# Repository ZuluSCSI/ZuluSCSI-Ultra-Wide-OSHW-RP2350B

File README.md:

ZuluSCSI™ Ultra Wide OSHW - Community Edition - Open Source Hardware
========================
ZuluSCSI Ultra Wide is the worlds first* OSHW _ultra wide_ SCSI emulator. It's an open-source alternative to our commercially-available [ZuluSCSI Wide](https://shop.rabbitholecomputing.com/blogs/news/zuluscsi-wide-33mb-sec-wide-scsi-emulator), which uses much higher-quality printed circuit boards and largely higher-quality components. 

ZuluSCSI Ultra Wide runs unmodified [ZuluSCSI Wide firmware](https://github.com/ZuluSCSI/ZuluSCSI-firmware/releases).

This repository contains the KiCAD 9 schematic and PCB design files for an Open Source Hardware variant of the RP2350B-based ZuluSCSI™ SCSI to SD storage emulator, derived from George Mezzomo's incomplete-at-time-of-forking [RP2350B-based GBSCSI2 wide board](https://github.com/GeorgeRudolf/GBSCSI2/tree/main/rp2350_HD68_3.5). 

Numerous small improvements to routing, pinouts, expansion headers, and power circuitry have been made. As always, firmware for ZuluSCSI is available at http://github.com/ZuluSCSI/ZuluSCSI-firmware

This hardware design is licensed under the terms of the strongly reciprocal CERN OHL-S V2 license, which can be viewed in full at https://ohwr.org/cern_ohl_s_v2.txt and https://ohwr.org/cern_ohl_s_v2.pdf. 

The Rev 2026b ZuluSCSI Ultra Wide OSHW design is [OSHWA-certified](https://certification.oshwa.org/us002798.html)

ZuluSCSI™ is a registered trademark of Rabbit Hole Computing, and may not be used commercially without the express written consent of Rabbit Hole Computing. Individuals producing ZuluSCSI boards for personal use are hereby granted permission to use the ZuluSCSI trademark in a noncommercial capacity.

_Any_ use of the ZuluSCSI trademark in a **commercial** context requires prior written consent from Rabbit Hole Computing.

* that we know of :)

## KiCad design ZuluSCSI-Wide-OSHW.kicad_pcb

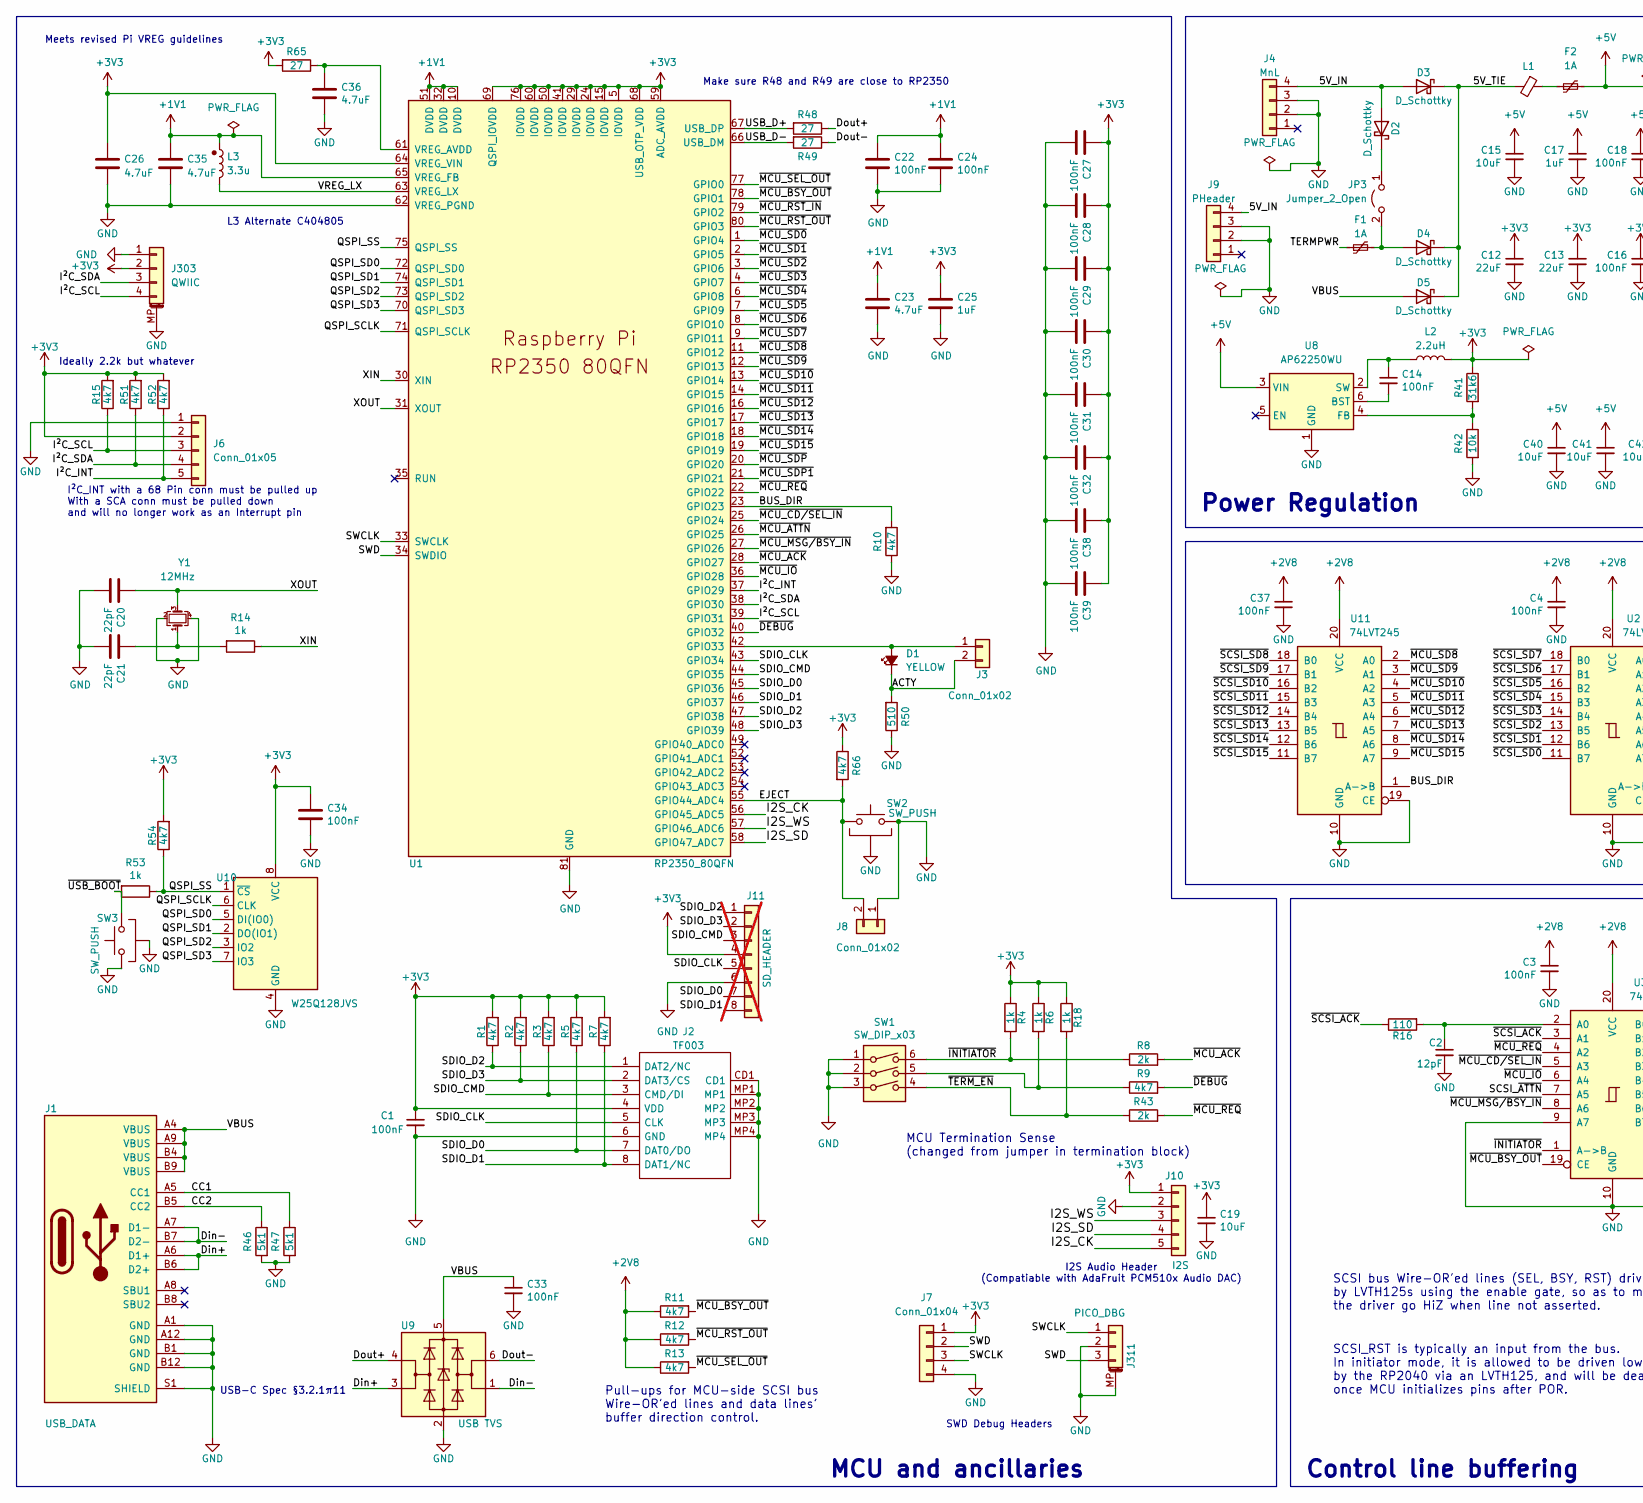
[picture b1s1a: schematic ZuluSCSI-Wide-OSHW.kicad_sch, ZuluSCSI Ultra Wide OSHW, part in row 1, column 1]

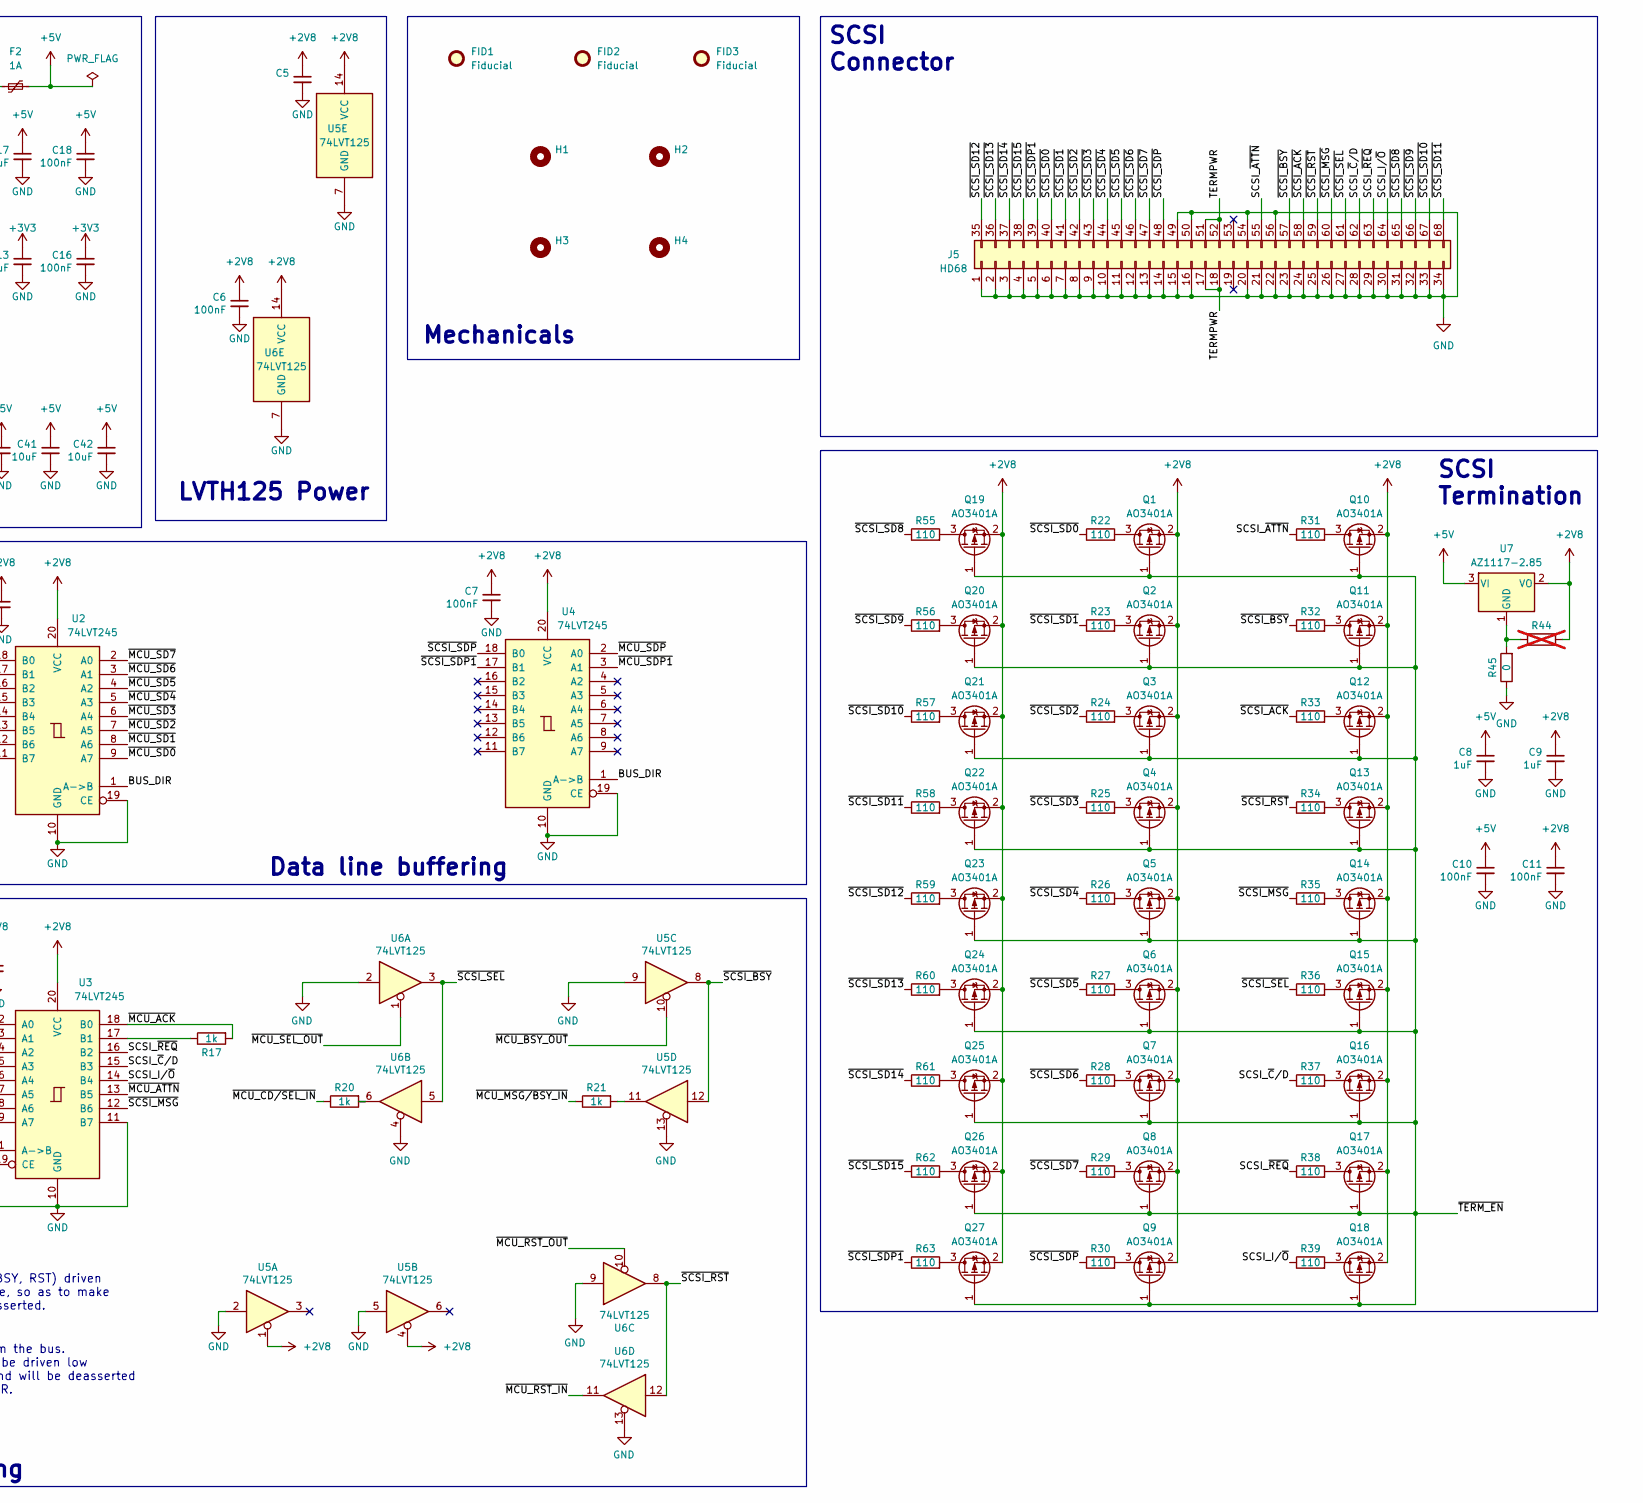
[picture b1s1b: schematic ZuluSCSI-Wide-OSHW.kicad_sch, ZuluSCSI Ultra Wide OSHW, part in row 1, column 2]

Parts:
C1, C3, C4, C5, C6, C7, C10, C11, C14, C16, C18, C37: 100nF; C_0603_1608Metric; LCSC C14663
C2: 12pF; C_0603_1608Metric; LCSC C38523
C8, C9, C17: 1uF; C_0603_1608Metric; LCSC C15849
C12, C13: 22uF; C_0603_1608Metric; LCSC C59461
C15, C19, C40, C41, C42: 10uF; C_0603_1608Metric; LCSC C96446
C20, C21: 22pF; C_0402_1005Metric; LCSC C1555
C22, C24, C27, C28, C29, C30, C31, C32, C33, C34, C38, C39: 100nF; C_0402_1005Metric; LCSC C307331
C23: 4.7uF; C_0402_1005Metric; LCSC C23733
C25: 1uF; C_0402_1005Metric; LCSC C52923
C26, C35: 4.7uF; C_0603_1608Metric; LCSC Part # C19666
C36: 4.7uF; C_0402_1005Metric; LCSC Part # C23733
D1: YELLOW; LED_0603_1608Metric; LCSC C72038
D2, D3, D4, D5: D_Schottky; D_SOD-123; LCSC C82544
F1, F2: 1A; Fuse_0805_2012Metric; LCSC C70061
FID1, FID2, FID3: Fiducial; Fiducial_0.5mm_Mask1mm; LCSC N/A
H1, H2, H3, H4: MH2.5_NPTH; LCSC N/A
J1: USB_DATA; USB_C_Receptacle_HRO_TYPE-C-31-M-12; LCSC C165948
J2: TF003; TF01A; LCSC C5155563
J3, J8: Conn_01x02; PinHeader_1x02_P2.54mm_Vertical; LCSC N/A
J4: MnL; DRVPWR; LCSC N/A
J5: HD68; 5787169-7; LCSC N/A
J6: Conn_01x05; PinHeader_1x05_P2.54mm_Vertical; LCSC N/A
J7: Conn_01x04; PinHeader_1x04_P2.54mm_Vertical; LCSC N/A
J9: PHeader; PinHeader_1x04_P2.54mm_Vertical; LCSC N/A
J10: I2S; PCM510x_1x05_P2.54mm_Vertical
J11: SD_HEADER; PinHeader_1x08_P2.54mm_Vertical; not fitted
J303: QWIIC; JST_SH_BM04B-SRSS-TB_1x04-1MP_P1.00mm_Vertical; LCSC C160390
J311: PICO_DBG; JST_SH_BM03B-SRSS-TB_1x03-1MP_P1.00mm_Vertical; LCSC C160389
JP3: Jumper_2_Open; PinHeader_2x01_P2.54mm_Vertical; LCSC N/A
L1: Ferrite_Bead_Small; L_0603_1608Metric; LCSC C1002
L2: 2.2uH; L_1008_2520Metric_Pad1.43x2.20mm_HandSolder; PartNumber DFE252012P-2R2M=P2; LCSC C86092
L3: 3.3u; L_pol_2016; PartNumber AOTA-B201610S3R3-101-T; digikey 535-AOTA-B201610S3R3-101-TTR-ND
Q1, Q2, Q3, Q4, Q5, Q6, Q7, Q8, Q9, Q10, Q11, Q12, Q13, Q14, Q15, Q16, Q17, Q18, Q19, Q20, Q21, Q22, Q23, Q24, Q25, Q26, Q27: AO3401A; SOT-23; LCSC C15127
R1, R2, R3, R5, R7, R9, R10, R11, R12, R13, R15, R51, R52, R54, R66: 4k7; R_0603_1608Metric; LCSC C23162
R4, R6, R17, R18, R20, R21: 1k; R_0603_1608Metric; LCSC C21190
R8, R43: 2k; R_0603_1608Metric; LCSC C22975
R14, R53: 1k; R_0402_1005Metric; LCSC C11702
R16, R22, R23, R24, R25, R26, R27, R28, R29, R30, R31, R32, R33, R34, R35, R36, R37, R38, R39, R55, R56, R57, R58, R59, R60, R61, R62, R63: 110; R_0603_1608Metric; LCSC C22781
R41: 31k6; R_0603_1608Metric; LCSC C25967
R42: 10k; R_0603_1608Metric; LCSC C25804
R44: R_0603_1608Metric; LCSC N/A; not fitted
R45: 0; R_0603_1608Metric; LCSC C21189
R46, R47: 5k1; R_0402_1005Metric; LCSC C25905
R48, R49, R65: 27; R_0402_1005Metric; LCSC C25092
R50: 510; R_0603_1608Metric; LCSC C23193
SW1: SW_DIP_x03; SW_DIP_SPSTx03_Slide_6.7x9.18mm_W8.61mm_P2.54mm_LowProfile; PartNumber 219-3MSTR; LCSC C319040
SW2, SW3: SW_PUSH; SW-SMD_GT-TC108A-H034-L1S; LCSC C22396279
U1: RP2350_80QFN; RP2350-QFN-80-1EP_10x10_P0.4mm_EP3.4x3.4mm_ThermalVias; LCSC Part # C42415655
U2, U3, U4, U11: 74LVT245; SSOP-20_5.3x7.2mm_P0.65mm; LCSC C74214
U5, U6: 74LVT125; TSSOP-14_4.4x5mm_P0.65mm; LCSC C7042
U7: AZ1117-2.85; SOT-223-3_TabPin2; LCSC C14791
U8: AP62250WU; TSOT-23-6; LCSC C5184228
U9: USB TVS; SOT-23-6; LCSC C2827654
U10: W25Q128JVS; SOIC-8_5.23x5.23mm_P1.27mm; LCSC C97521
Y1: 12MHz; Crystal_SMD_3225-4Pin_3.2x2.5mm; PartNumber ABM8-272-T3; LCSC C20625731

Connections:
+1V1: C22.1, C23.1, C24.1, C35.1, L3.1, U1.10 (DVDD), U1.32 (DVDD), U1.51 (DVDD), U1.65 (VREG_FB)
+2V8: C3.1, C4.1, C5.1, C6.1, C7.1, C9.1, C11.1, C37.1, Q1.2 (S), Q2.2 (S), Q3.2 (S), Q4.2 (S), Q5.2 (S), Q6.2 (S), Q7.2 (S), Q8.2 (S), Q9.2 (S), Q10.2 (S), Q11.2 (S), Q12.2 (S), Q13.2 (S), Q14.2 (S), Q15.2 (S), Q16.2 (S), Q17.2 (S), Q18.2 (S), Q19.2 (S), Q20.2 (S), Q21.2 (S), Q22.2 (S), Q23.2 (S), Q24.2 (S), Q25.2 (S), Q26.2 (S), Q27.2 (S), R11.1, R12.1, R13.1, R44.2, U2.20 (VCC), U3.20 (VCC), U4.20 (VCC), U5.1, U5.4, U5.14 (VCC), U6.14 (VCC), U7.2 (VO), U11.20 (VCC)
+3V3: C1.1, C12.1, C13.1, C16.1, C19.1, C25.1, C26.1, C27.1, C28.1, C29.1, C30.1, C31.1, C32.1, C34.1, C38.1, C39.1, J2.4 (VDD), J6.2, J7.1, J10.1, J11.4, J303.2, L2.2, R1.2, R2.2, R3.2, R4.1, R5.2, R6.1, R7.2, R15.2, R18.1, R41.1, R51.2, R52.2, R54.2, R65.2, R66.1, U1.5 (IOVDD), U1.15 (IOVDD), U1.24 (IOVDD), U1.29 (IOVDD), U1.41 (IOVDD), U1.50 (IOVDD), U1.59 (ADC_AVDD), U1.60 (IOVDD), U1.64 (VREG_VIN), U1.68 (USB_OTP_VDD), U1.69 (QSPI_IOVDD), U1.76 (IOVDD), U10.8 (VCC)
+5V: C8.1, C10.1, C15.1, C17.1, C18.1, C40.1, C41.1, C42.1, F2.2, U7.3 (VI), U8.3 (VIN)
/5V_IN: D2.2 (A), D3.2 (A), J4.4, J9.4
/5V_TIE: D3.1 (K), D4.1 (K), D5.1 (K), L1.2
/ACTY: D1.1 (K), J3.2, R50.2
/BUS_DIR: R10.2, U1.23 (GPIO23), U2.1 (A->B), U4.1 (A->B), U11.1 (A->B)
/CC1: J1.A5 (CC1), R47.1
/CC2: J1.B5 (CC2), R46.1
/Din+: J1.A6 (D1+), J1.B6 (D2+), U9.3 (I/O2)
/Din-: J1.A7 (D1-), J1.B7 (D2-), U9.1 (I/O1)
/Dout+: R48.1, U9.4 (I/O2)
/Dout-: R49.1, U9.6 (I/O1)
/EJECT: J8.2, R66.2, SW2.2, U1.55 (GPIO44_ADC4)
/I2S_CK: J10.5, U1.56 (GPIO45_ADC5)
/I2S_SD: J10.4, U1.58 (GPIO47_ADC7)
/I2S_WS: J10.3, U1.57 (GPIO46_ADC6)
/I²C_INT: J6.5, R52.1, U1.37 (GPIO29)
/I²C_SCL: J6.3, J303.4, R15.1, U1.39 (GPIO31)
/I²C_SDA: J6.4, J303.3, R51.1, U1.38 (GPIO30)
/QSPI_SCLK: U1.71 (QSPI_SCLK), U10.6 (CLK)
/QSPI_SD0: U1.72 (QSPI_SD0), U10.5 (DI(IO0))
/QSPI_SD1: U1.74 (QSPI_SD1), U10.2 (DO(IO1))
/QSPI_SD2: U1.73 (QSPI_SD2), U10.3 (IO2)
/QSPI_SD3: U1.70 (QSPI_SD3), U10.7 (IO3)
/QSPI_SS: R53.1, R54.1, U1.75 (QSPI_SS), U10.1 (~CS)
/SCSI_I/~O: J5.64, R39.1, U3.14 (B4)
/SCSI_~ATTN: J5.55, R31.1, U3.7 (A5)
/SCSI_~C/D: J5.62, R37.1, U3.15 (B3)
/SCSI_~REQ: J5.63, R38.1, U3.16 (B2)
/SDIO_CLK: J2.5 (CLK), J11.5, U1.43 (GPIO34)
/SDIO_CMD: J2.3 (CMD/DI), J11.3, R3.1, U1.44 (GPIO35)
/SDIO_D0: J2.7 (DAT0/DO), J11.7, R5.1, U1.45 (GPIO36)
/SDIO_D1: J2.8 (DAT1/NC), J11.8, R7.1, U1.46 (GPIO37)
/SDIO_D2: J2.1 (DAT2/NC), J11.1, R1.1, U1.47 (GPIO38)
/SDIO_D3: J2.2 (DAT3/CS), J11.2, R2.1, U1.48 (GPIO39)
/SWCLK: J7.3, J311.1, U1.33 (SWCLK)
/SWD: J7.2, J311.3, U1.34 (SWDIO)
/TERMPWR: F1.1, J5.17, J5.18, J5.51, J5.52
/USB_D+: R48.2, U1.67 (USB_DP)
/USB_D-: R49.2, U1.66 (USB_DM)
/VBUS: C33.1, D5.2 (A), J1.A4 (VBUS), J1.A9 (VBUS), J1.B4 (VBUS), J1.B9 (VBUS), U9.5 (VBUS)
/VREG_LX: L3.2, U1.63 (VREG_LX)
/XIN: R14.1, U1.30 (XIN)
/XOUT: C20.1, U1.31 (XOUT), Y1.3
/~DEBUG: R9.2, U1.40 (GPIO32)
/~INITIATOR: R4.2, R8.1, SW1.6, U3.1 (A->B)
/~MCU_ACK: R8.2, R17.2, U1.28 (GPIO27), U3.18 (B0)
/~MCU_ATTN: U1.26 (GPIO25), U3.13 (B5)
/~MCU_BSY_OUT: R11.2, U1.78 (GPIO1), U3.19 (CE), U5.10
/~MCU_CD/SEL_IN: R20.1, U1.25 (GPIO24), U3.5 (A3)
/~MCU_IO: U1.36 (GPIO28), U3.6 (A4)
/~MCU_MSG/BSY_IN: R21.1, U1.27 (GPIO26), U3.8 (A6)
/~MCU_REQ: R43.2, U1.22 (GPIO22), U3.4 (A2)
/~MCU_RST_IN: U1.79 (GPIO2), U6.11
/~MCU_RST_OUT: R12.2, U1.80 (GPIO3), U6.10
/~MCU_SD0: U1.1 (GPIO4), U2.9 (A7)
/~MCU_SD1: U1.2 (GPIO5), U2.8 (A6)
/~MCU_SD2: U1.3 (GPIO6), U2.7 (A5)
/~MCU_SD3: U1.4 (GPIO7), U2.6 (A4)
/~MCU_SD4: U1.6 (GPIO8), U2.5 (A3)
/~MCU_SD5: U1.7 (GPIO9), U2.4 (A2)
/~MCU_SD6: U1.8 (GPIO10), U2.3 (A1)
/~MCU_SD7: U1.9 (GPIO11), U2.2 (A0)
/~MCU_SD8: U1.11 (GPIO12), U11.2 (A0)
/~MCU_SD9: U1.12 (GPIO13), U11.3 (A1)
/~MCU_SD10: U1.13 (GPIO14), U11.4 (A2)
/~MCU_SD11: U1.14 (GPIO15), U11.5 (A3)
/~MCU_SD12: U1.16 (GPIO16), U11.6 (A4)
/~MCU_SD13: U1.17 (GPIO17), U11.7 (A5)
/~MCU_SD14: U1.18 (GPIO18), U11.8 (A6)
/~MCU_SD15: U1.19 (GPIO19), U11.9 (A7)
/~MCU_SDP1: U1.21 (GPIO21), U4.3 (A1)
/~MCU_SDP: U1.20 (GPIO20), U4.2 (A0)
/~MCU_SEL_OUT: R13.2, U1.77 (GPIO0), U6.1
/~SCSI_ACK: J5.58, R16.1, R33.1, U3.3 (A1)
/~SCSI_BSY: J5.57, R32.1, U5.8, U5.12
/~SCSI_MSG: J5.60, R35.1, U3.12 (B6)
/~SCSI_RST: J5.59, R34.1, U6.8, U6.12
/~SCSI_SD0: J5.40, R22.1, U2.11 (B7)
/~SCSI_SD1: J5.41, R23.1, U2.12 (B6)
/~SCSI_SD2: J5.42, R24.1, U2.13 (B5)
/~SCSI_SD3: J5.43, R25.1, U2.14 (B4)
/~SCSI_SD4: J5.44, R26.1, U2.15 (B3)
/~SCSI_SD5: J5.45, R27.1, U2.16 (B2)
/~SCSI_SD6: J5.46, R28.1, U2.17 (B1)
/~SCSI_SD7: J5.47, R29.1, U2.18 (B0)
/~SCSI_SD8: J5.65, R55.1, U11.18 (B0)
/~SCSI_SD9: J5.66, R56.1, U11.17 (B1)
/~SCSI_SD10: J5.67, R57.1, U11.16 (B2)
/~SCSI_SD11: J5.68, R58.1, U11.15 (B3)
/~SCSI_SD12: J5.35, R59.1, U11.14 (B4)
/~SCSI_SD13: J5.36, R60.1, U11.13 (B5)
/~SCSI_SD14: J5.37, R61.1, U11.12 (B6)
/~SCSI_SD15: J5.38, R62.1, U11.11 (B7)
/~SCSI_SDP1: J5.39, R63.1, U4.17 (B1)
/~SCSI_SDP: J5.48, R30.1, U4.18 (B0)
/~SCSI_SEL: J5.61, R36.1, U6.3, U6.5
/~TERM_EN: Q1.1 (G), Q2.1 (G), Q3.1 (G), Q4.1 (G), Q5.1 (G), Q6.1 (G), Q7.1 (G), Q8.1 (G), Q9.1 (G), Q10.1 (G), Q11.1 (G), Q12.1 (G), Q13.1 (G), Q14.1 (G), Q15.1 (G), Q16.1 (G), Q17.1 (G), Q18.1 (G), Q19.1 (G), Q20.1 (G), Q21.1 (G), Q22.1 (G), Q23.1 (G), Q24.1 (G), Q25.1 (G), Q26.1 (G), Q27.1 (G), R18.2, R43.1, SW1.4
/~USB_BOOT: R53.2, SW3.2
GND: C1.2, C2.2, C3.2, C4.2, C5.2, C6.2, C7.2, C8.2, C9.2, C10.2, C11.2, C12.2, C13.2, C15.2, C16.2, C17.2, C18.2, C19.2, C20.2, C21.2, C22.2, C23.2, C24.2, C25.2, C26.2, C27.2, C28.2, C29.2, C30.2, C31.2, C32.2, C33.2, C34.2, C35.2, C36.2, C37.2, C38.2, C39.2, C40.2, C41.2, C42.2, J1.A1 (GND), J1.A12 (GND), J1.B1 (GND), J1.B12 (GND), J1.S1 (SHIELD), J2.6 (GND), J2.CD1, J2.MP1, J2.MP2, J2.MP3, J2.MP4, J4.2, J4.3, J5.1, J5.2, J5.3, J5.4, J5.5, J5.6, J5.7, J5.8, J5.9, J5.10, J5.11, J5.12, J5.13, J5.14, J5.15, J5.16, J5.20, J5.21, J5.22, J5.23, J5.24, J5.25, J5.26, J5.27, J5.28, J5.29, J5.30, J5.31, J5.32, J5.33, J5.34, J5.49, J5.50, J5.54, J5.56, J6.1, J7.4, J8.1, J9.2, J9.3, J10.2, J11.6, J303.1, J303.MP (MountPin), J311.2, J311.MP (MountPin), R10.1, R42.2, R45.1, R46.2, R47.2, R50.1, SW1.1, SW1.2, SW1.3, SW2.1, SW2.3 (MNT), SW3.1, SW3.3 (MNT), U1.62 (VREG_PGND), U1.81 (GND), U2.10 (GND), U2.19 (CE), U3.9 (A7), U3.10 (GND), U3.11 (B7), U4.10 (GND), U4.19 (CE), U5.2, U5.5, U5.7 (GND), U5.9, U5.13, U6.2, U6.4, U6.7 (GND), U6.9, U6.13, U8.1 (GND), U9.2 (GND), U10.4 (GND), U11.10 (GND), U11.19 (CE), Y1.2, Y1.4
unnamed: C21.1, R14.2, Y1.1
unnamed: D1.2 (A), J3.1, U1.42 (GPIO33)
unnamed: D2.1 (K), JP3.1 (A)
unnamed: D4.2 (A), F1.2, JP3.2 (B)
unnamed: F2.1, L1.1
unnamed: Q1.3 (D), R22.2
unnamed: Q2.3 (D), R23.2
unnamed: Q3.3 (D), R24.2
unnamed: Q4.3 (D), R25.2
unnamed: Q5.3 (D), R26.2
unnamed: Q6.3 (D), R27.2
unnamed: Q7.3 (D), R28.2
unnamed: Q8.3 (D), R29.2
unnamed: Q9.3 (D), R30.2
unnamed: Q10.3 (D), R31.2
unnamed: Q11.3 (D), R32.2
unnamed: Q12.3 (D), R33.2
unnamed: Q13.3 (D), R34.2
unnamed: Q14.3 (D), R35.2
unnamed: Q15.3 (D), R36.2
unnamed: Q16.3 (D), R37.2
unnamed: Q17.3 (D), R38.2
unnamed: Q18.3 (D), R39.2
unnamed: Q19.3 (D), R55.2
unnamed: Q20.3 (D), R56.2
unnamed: Q21.3 (D), R57.2
unnamed: Q22.3 (D), R58.2
unnamed: Q23.3 (D), R59.2
unnamed: Q24.3 (D), R60.2
unnamed: Q25.3 (D), R61.2
unnamed: Q26.3 (D), R62.2
unnamed: Q27.3 (D), R63.2
unnamed: R6.2, R9.1, SW1.5
unnamed: R20.2, U6.6
unnamed: R21.2, U5.11
unnamed: C36.1, R65.1, U1.61 (VREG_AVDD)
unnamed: C2.1, R16.2, U3.2 (A0)
unnamed: R17.1, U3.17 (B1)
unnamed: R44.1, R45.2, U7.1 (GND)
unnamed: C14.2, U8.6 (BST)
unnamed: R41.2, R42.1, U8.4 (FB)
unnamed: C14.1, L2.1, U8.2 (SW)

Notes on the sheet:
Pull-ups for MCU-side SCSI bus Wire-OR'ed lines and data lines' buffer direction control.
Meets revised Pi VREG guidelines
MCU and ancillaries
SCSI_RST is typically an input from the bus. In initiator mode, it is allowed to be driven low by the RP2040 via an LVTH125, and will be deasserted once MCU initializes pins after POR.
Data line buffering
LVTH125 Power
I2S Audio Header (Compatiable with AdaFruit PCM510x Audio DAC)
Power Regulation
SCSI Connector
L3 Alternate C404805
I²C_INT with a 68 Pin conn must be pulled up With a SCA conn must be pulled down and will no longer work as an Interrupt pin
USB-C Spec §3.2.1¶11
Mechanicals
SWD Debug Headers
Ideally 2.2k but whatever
MCU Termination Sense (changed from jumper in termination block)
Control line buffering
SCSI bus Wire-OR'ed lines (SEL, BSY, RST) driven by LVTH125s using the enable gate, so as to make the driver go HiZ when line not asserted.
Make sure R48 and R49 are close to RP2350
SCSI Termination

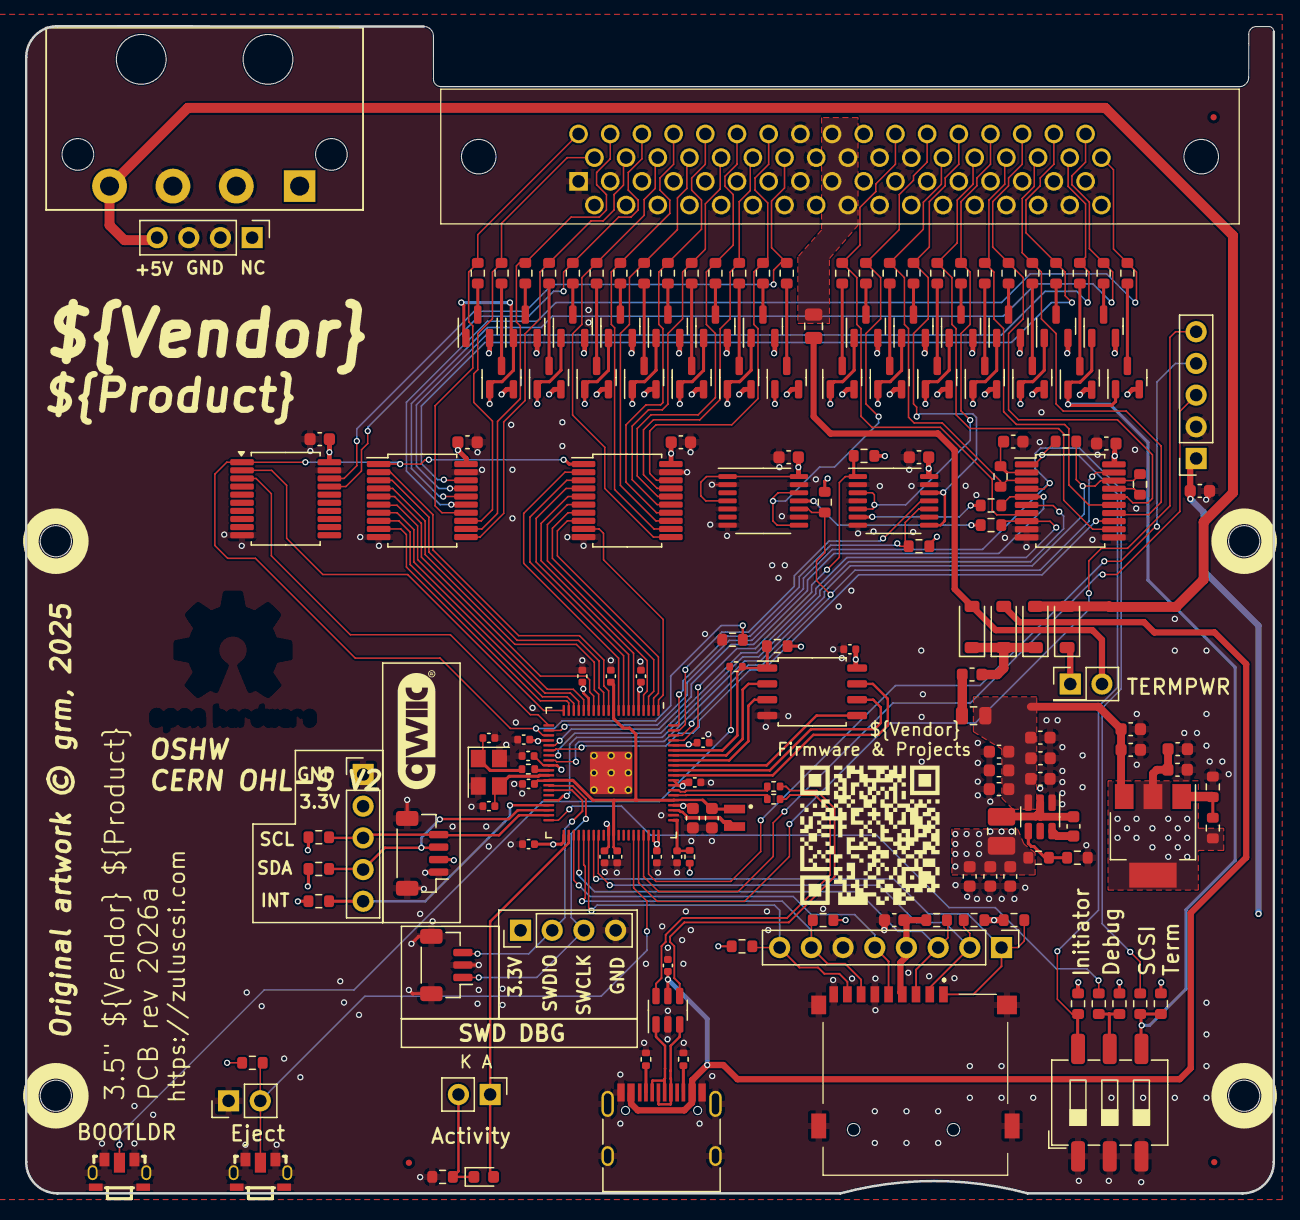
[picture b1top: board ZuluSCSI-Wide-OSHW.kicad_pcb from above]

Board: 4 copper layers, 100.0 x 93.5 mm, 178 parts (0 on the bottom side), 144 nets.

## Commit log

2025-03-10 Initial import of ZuluSCSI Wide OSHW, an RP2350B-based Fast Wide SCSI emulator
    This design is derived from George Mezzomo's RP2350B-based GBSCSI2 wide board, as located at https://github.com/GeorgeRudolf/GBSCSI2/tree/main/rp2350_HD68_3.5
2025-03-10 Switch fonts, modify silkscreen
2025-04-14 Update schematic
2025-06-04 Make board ZuluSCSI firmware compatible
    The initial design of the Wide OSHW had pin differences that were
    incompatible with unmodified ZuluSCSI firmware with wide support.
    The following changes were made:
    - The BUS_DIR changed polarity in the wide firmware thus the A and B
    side on the data buffers had to be swapped
    - 74LVT125 could no longer be used to for the parity pins on the
2026-01-10 PCB Update, Layout and DRC passed for rev 2026a
    Schematic updated with more features from the ZuluSCSI wide board.
    JLCPCB parts orientation and position adjusted.
    Silkscreen updated
    Features added:
    - Pico SWD debug header (3 Pin JST header)
    - I2C QWIIC header added (4 pin JST header)
2026-01-19 Improvements to ZuluSCSI Ultra Wide OSHW
    Expanded the description of ZuluSCSI Ultra Wide to include improvements
    and compatibility notes.
    Added CERN Open Hardware Licence Version 2 - Strongly Reciprocal
    (Strict Variant, OHL-S v2) to the project.
    Changes to PCB and Schematic
    - Added missing 3d models of parts
2026-01-19 Prepare for initial ZuluSCSI Ultra Wide OSHW public release
    Updated project description and trademark information.
2026-01-20 Revise README content for better clarity
    Updated the README to improve clarity and organization of information.
2026-01-20 fix typo
2026-01-29 Add OSHWA certification deatils
    The Rev 2026b ZuluSCSI Ultra Wide OSHW design is OSHWA-certified. See https://certification.oshwa.org/us002798.html
2026-01-29 Include OSHWA certification reference in README
    Added OSHWA certification image to README.
2026-02-06 Enhance README with ZuluSCSI Ultra Wide information
    Added details about ZuluSCSI Ultra Wide and its features.

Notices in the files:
ZuluSCSI-Wide-OSHW.kicad_pcb:
Original artwork © grm, 2025
